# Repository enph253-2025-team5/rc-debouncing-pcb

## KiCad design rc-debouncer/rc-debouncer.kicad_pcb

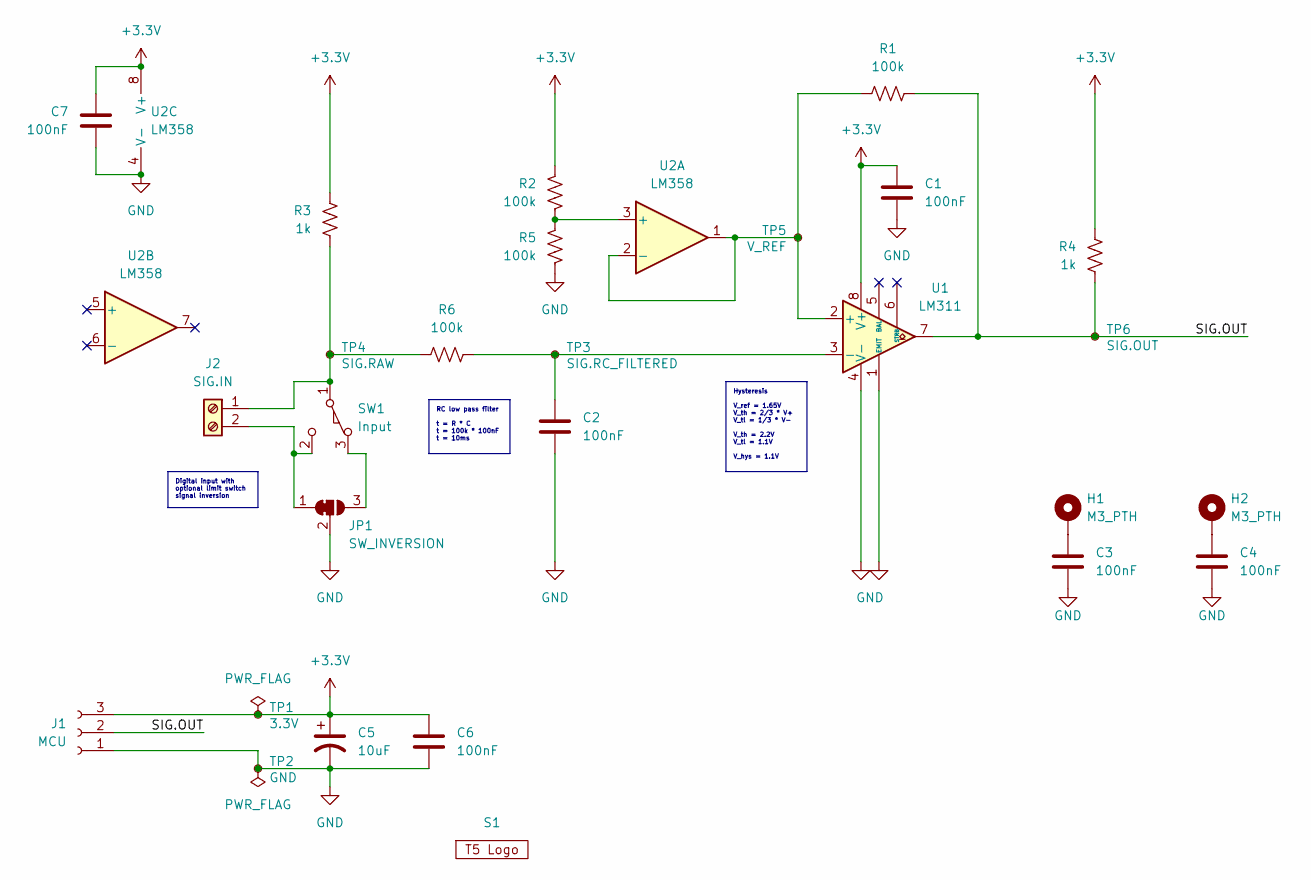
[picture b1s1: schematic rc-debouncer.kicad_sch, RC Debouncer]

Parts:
C1, C2, C3, C4, C6, C7: 100nF; C_Disc_D3.0mm_W2.0mm_P2.50mm
C5: 10uF; CP_Radial_D5.0mm_P2.00mm
H1, H2: M3_PTH; MountingHole_3.2mm_M3_Pad
J1: MCU; JST_XH_S3B-XH-A-1_1x03_P2.50mm_Horizontal
J2: SIG.IN; TerminalBlock_Xinya_XY308-2.54-2P_1x02_P2.54mm_Horizontal
JP1: SW_INVERSION; SolderJumper-3_P1.3mm_Bridged12_RoundedPad1.0x1.5mm
R1, R2, R5, R6: 100k; R_Axial_DIN0309_L9.0mm_D3.2mm_P12.70mm_Horizontal
R3, R4: 1k; R_Axial_DIN0309_L9.0mm_D3.2mm_P12.70mm_Horizontal
S1: Logo; ENPH253_Logo
SW1: Input; SW_XKB_DM1-16UP-1
TP1: 3.3V; TestPoint_Pad_1.5x1.5mm
TP2: GND; TestPoint_Pad_1.5x1.5mm
TP3: SIG.RC_FILTERED; TestPoint_Pad_1.5x1.5mm
TP4: SIG.RAW; TestPoint_Pad_1.5x1.5mm
TP5: V_REF; TestPoint_Pad_1.5x1.5mm
TP6: SIG.OUT; TestPoint_Pad_1.5x1.5mm
U1: LM311; DIP-8_W7.62mm_LongPads
U2: LM358; DIP-8_W7.62mm_LongPads

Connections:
+3.3V: C1.1, C5.1, C6.1, C7.1, J1.3, R2.2, R3.1, R4.1, TP1.1, U1.8 (V+), U2.8 (V+)
/SIG.OUT: J1.2, R1.1, R4.2, TP6.1, U1.7
GND: C1.2, C2.2, C3.2, C4.2, C5.2, C6.2, C7.2, J1.1, JP1.2 (C), R5.1, TP2.1, U1.1 (EMIT), U1.4 (V-), U2.4 (V-)
unnamed: C3.1, H1.1
unnamed: C4.1, H2.1
unnamed: J2.1, R3.2, R6.1, SW1.1 (C), TP4.1
unnamed: J2.2, JP1.1 (A), SW1.2 (NO)
unnamed: JP1.3 (B), SW1.3 (NC)
unnamed: R1.2, TP5.1, U1.2 (+), U2.1, U2.2 (-)
unnamed: C2.1, R6.2, TP3.1, U1.3 (-)
unnamed: R2.1, R5.2, U2.3 (+)

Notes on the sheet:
RC low pass filter t = R * C t = 100k * 100nF t = 10ms
Hysteresis V_ref = 1.65V V_th = 2/3 * V+ V_tl = 1/3 * V- V_th = 2.2V V_tl = 1.1V V_hys = 1.1V
Digital input with optional limit switch signal inversion

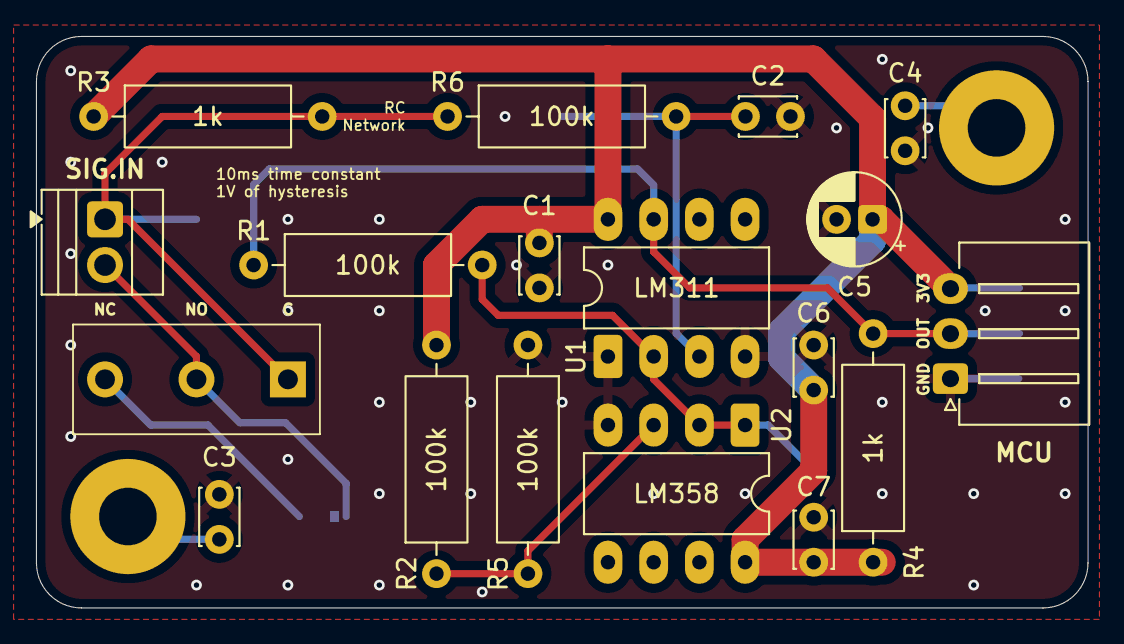
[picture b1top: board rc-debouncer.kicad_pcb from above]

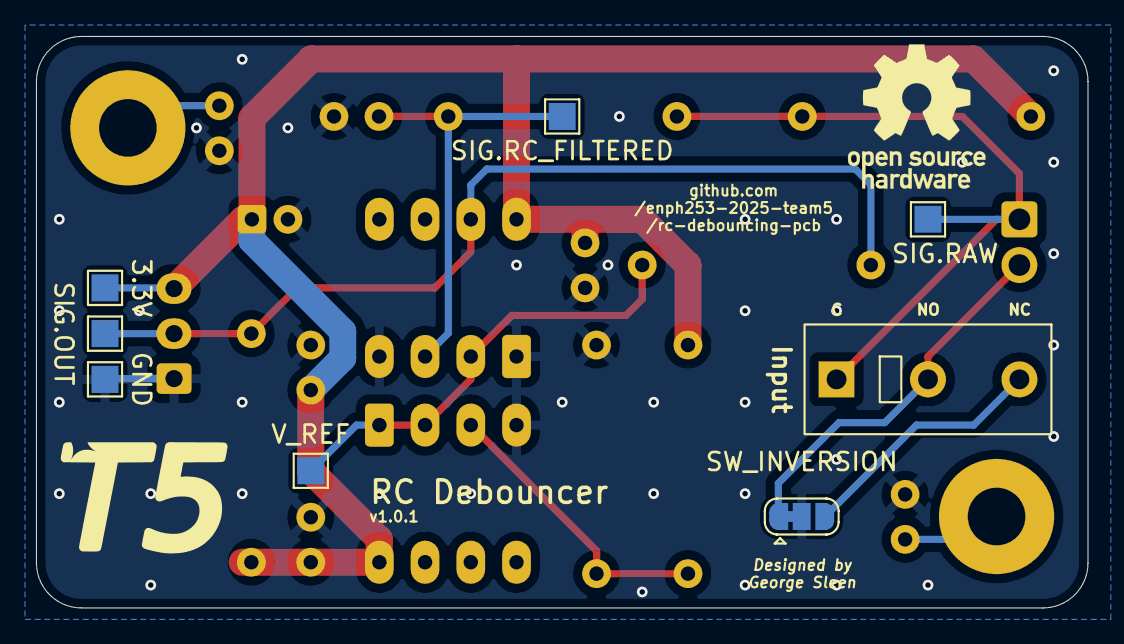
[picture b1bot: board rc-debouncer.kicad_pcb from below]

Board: 2 copper layers, 58.4 x 31.8 mm, 28 parts (9 on the bottom side), 11 nets.

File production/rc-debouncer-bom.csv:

"Value","Qty","Reference","Footprint"
"100nF","6","C1,C2,C3,C4,C6,C7","Capacitor_THT:C_Disc_D3.0mm_W2.0mm_P2.50mm"
"MCU","1","J1","GS_Connectors:JST_XH_S3B-XH-A-1_1x03_P2.50mm_Horizontal"
"SIG.IN","1","J2","TerminalBlock:TerminalBlock_Xinya_XY308-2.54-2P_1x02_P2.54mm_Horizontal"
"Input","1","SW1","Button_Switch_THT:SW_XKB_DM1-16UP-1"
"LM358","1","U2","Package_DIP:DIP-8_W7.62mm_LongPads"
"10uF","1","C5","Capacitor_THT:CP_Radial_D5.0mm_P2.00mm"
"100k","4","R1,R2,R5,R6","Resistor_THT:R_Axial_DIN0309_L9.0mm_D3.2mm_P12.70mm_Horizontal"
"1k","2","R3,R4","Resistor_THT:R_Axial_DIN0309_L9.0mm_D3.2mm_P12.70mm_Horizontal"
"LM311","1","U1","Package_DIP:DIP-8_W7.62mm_LongPads"

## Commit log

2025-06-25 Update .gitignore to not ignore production outputs
2025-06-25 Initialize KiCad project
2025-07-01 Layout first revision
2025-07-04 Finish layout and generate production outputs
2025-07-06 Update back silkscreen to include revision
